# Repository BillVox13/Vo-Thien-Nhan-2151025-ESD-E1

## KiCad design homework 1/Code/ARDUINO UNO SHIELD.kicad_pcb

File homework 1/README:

All the project files are in the 'Project files' folder, the folder 'image' contains 4 different views of 3D image of the board.

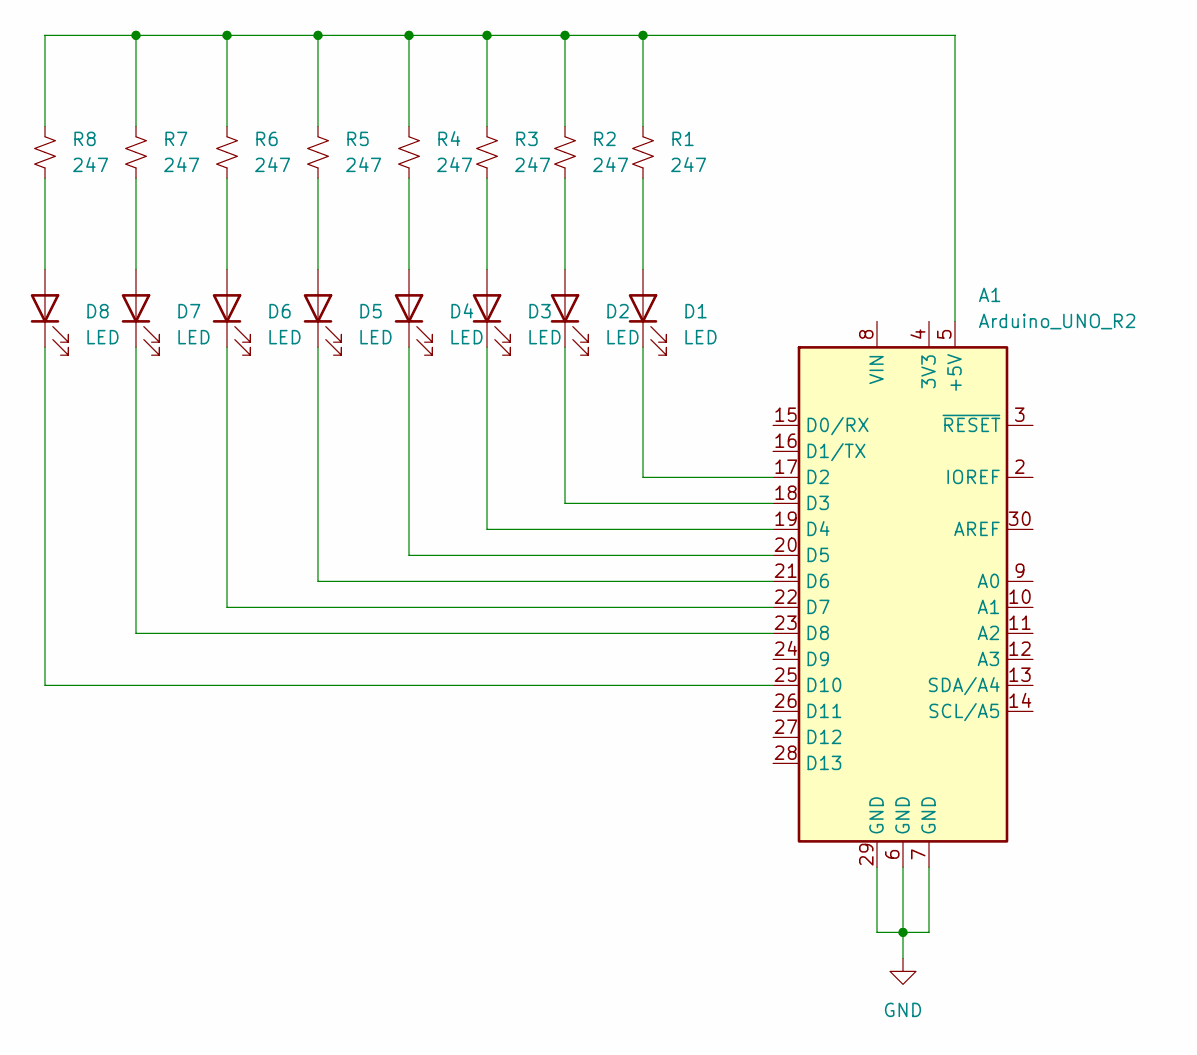
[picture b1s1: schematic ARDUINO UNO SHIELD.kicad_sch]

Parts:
A1: Arduino_UNO_R2
D1, D2, D3, D4, D5, D6, D7, D8: LED; LED_0805_2012Metric
R1, R2, R3, R4, R5, R6, R7, R8: 247; R_0603_1608Metric

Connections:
GND: A1.6 (GND), A1.7 (GND), A1.29 (GND)
unnamed: A1.5 (+5V), R1.1, R2.1, R3.1, R4.1, R5.1, R6.1, R7.1, R8.1
unnamed: A1.17 (D2), D1.1 (K)
unnamed: A1.18 (D3), D2.1 (K)
unnamed: A1.19 (D4), D3.1 (K)
unnamed: A1.20 (D5), D4.1 (K)
unnamed: A1.21 (D6), D5.1 (K)
unnamed: A1.22 (D7), D6.1 (K)
unnamed: A1.23 (D8), D7.1 (K)
unnamed: A1.25 (D10), D8.1 (K)
unnamed: D1.2 (A), R1.2
unnamed: D2.2 (A), R2.2
unnamed: D3.2 (A), R3.2
unnamed: D4.2 (A), R4.2
unnamed: D5.2 (A), R5.2
unnamed: D6.2 (A), R6.2
unnamed: D7.2 (A), R7.2
unnamed: D8.2 (A), R8.2

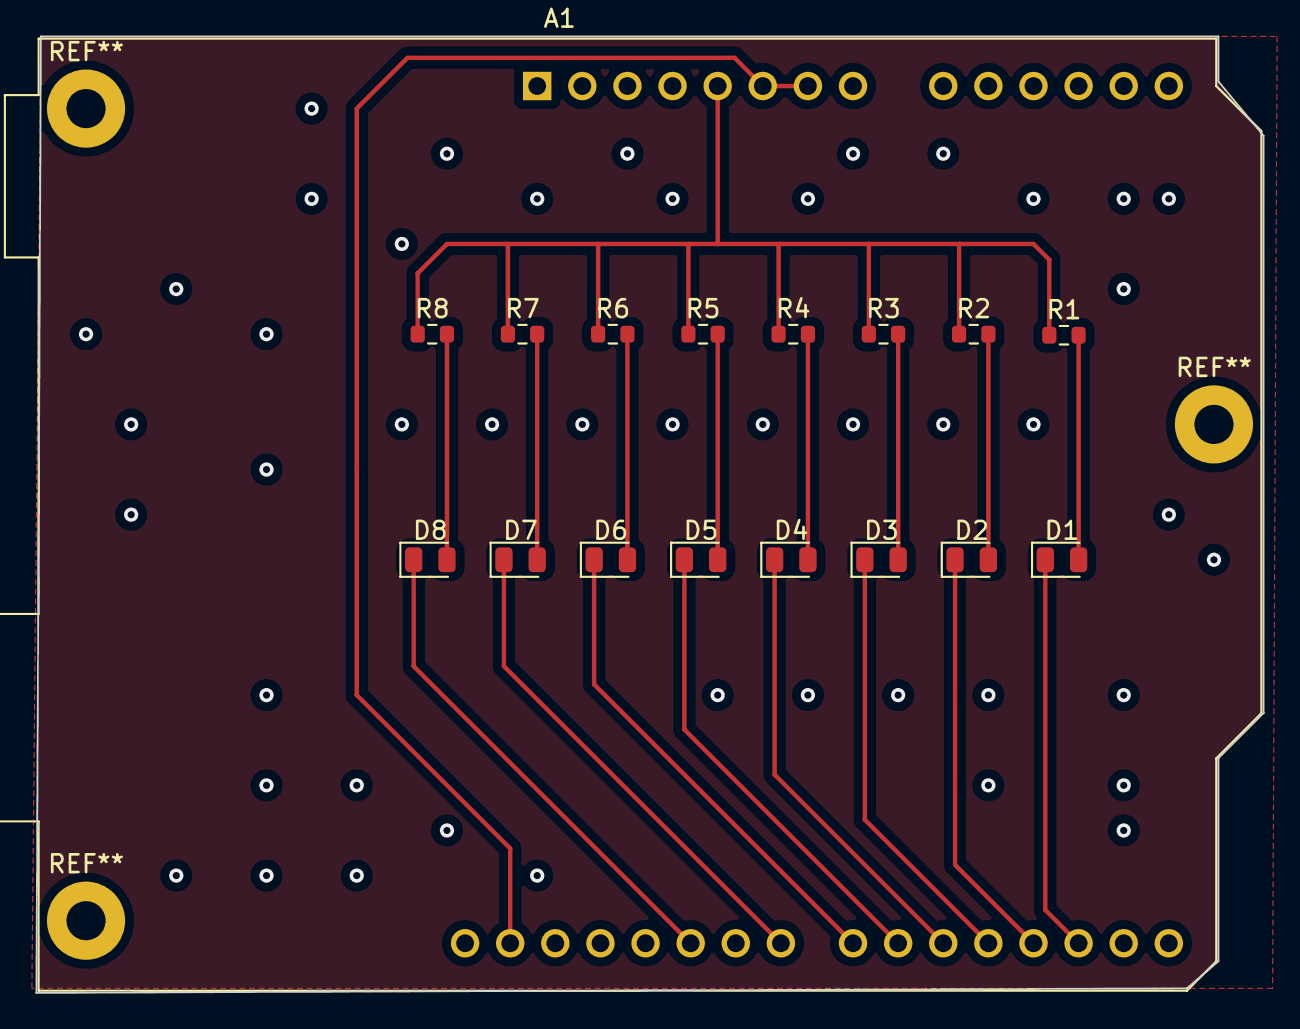
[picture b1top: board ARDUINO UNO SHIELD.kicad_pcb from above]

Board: 2 copper layers, 69.1 x 53.8 mm, 17 parts (0 on the bottom side), 18 nets.

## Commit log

2024-01-13 Create Homework 1
2024-01-13 Create Test
2024-01-14 homework 1/Code/ARDUINO UNO SHIELD.kicad_pcb
